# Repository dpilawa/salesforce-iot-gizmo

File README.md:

# salesforce-iot-gizmo

ESP8266-based sensor board for Salesforce IoT Cloud demos.

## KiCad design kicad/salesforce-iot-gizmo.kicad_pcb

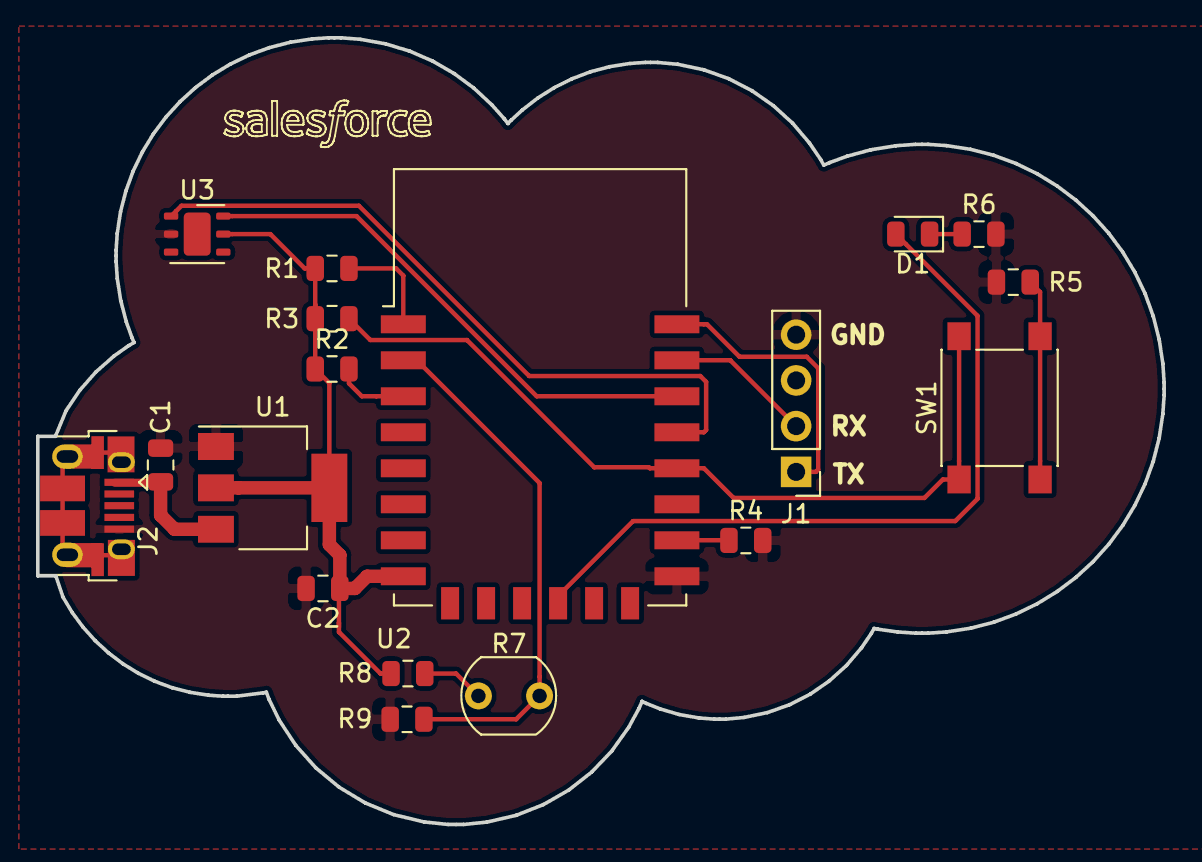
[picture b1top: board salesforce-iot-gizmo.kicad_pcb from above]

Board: 2 copper layers, 62.6 x 43.7 mm, 18 parts (0 on the bottom side), 16 nets.

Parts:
C1, C2: 10u; C_0805_2012Metric
D1: LED; LED_0805_2012Metric
J1: Conn_01x04_Male; PinHeader_1x04_P2.54mm_Vertical
J2: USB_B_Micro; USB_Micro-B_Amphenol_10103594-0001LF_Horizontal
R1, R2, R3, R4: 10k; R_0805_2012Metric
R5: 470; R_0805_2012Metric
R6: 150; R_0805_2012Metric
R7: R_PHOTO; R_LDR_5.1x4.3mm_P3.4mm_Vertical
R8: 220k; R_0805_2012Metric
R9: 100k; R_0805_2012Metric
SW1: SW_Push_Dual; SW_SPST_PTS645
U1: AP1117-33; SOT-223-3_TabPin2
U2: ESP-12E
U3: SHT20; DFN-6-1EP_3x3mm_P1mm_EP1.5x2.4mm

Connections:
+3V3: C2.1, R1.1, R2.1, R3.1, R8.1, U1.2, U2.8, U3.5
+5V: C1.1, J2.1, U1.3
/RX: J1.2, U2.21
/TX: J1.1, U2.22
GND: C1.2, C2.2, J1.4, J2.5, R4.2, R5.2, R6.2, R9.2, U1.1, U2.15, U3.2
unnamed: D1.1, R6.1
unnamed: D1.2, U2.12
unnamed: R1.2, U2.1
unnamed: R2.2, U2.3
unnamed: R3.2, SW1.1, U2.18
unnamed: R4.1, U2.16
unnamed: R5.1, SW1.2
unnamed: R7.1, R8.2
unnamed: R7.2, R9.1, U2.2
unnamed: U2.19, U3.1
unnamed: U2.20, U3.6

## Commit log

2019-01-07 added sym-lib-table
2019-01-07 folder reorg
2019-01-07 firmware configurator
2019-01-08 configurator cleanup
